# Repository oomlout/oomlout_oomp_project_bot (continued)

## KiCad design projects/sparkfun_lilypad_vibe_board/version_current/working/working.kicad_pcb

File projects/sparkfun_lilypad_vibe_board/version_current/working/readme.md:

# LilyPad_Vibe_Board by sparkfun  
This is a harvested standardized copy of a project from github.  
The original project can be found at:  
https://github.com/sparkfun/LilyPad_Vibe_Board  
Please consult that link for additional, details, files, and license information.  
Note: It was auto harvested and if the original repo had more than one board file or anything out of the ordinary the files here are likely not representative.

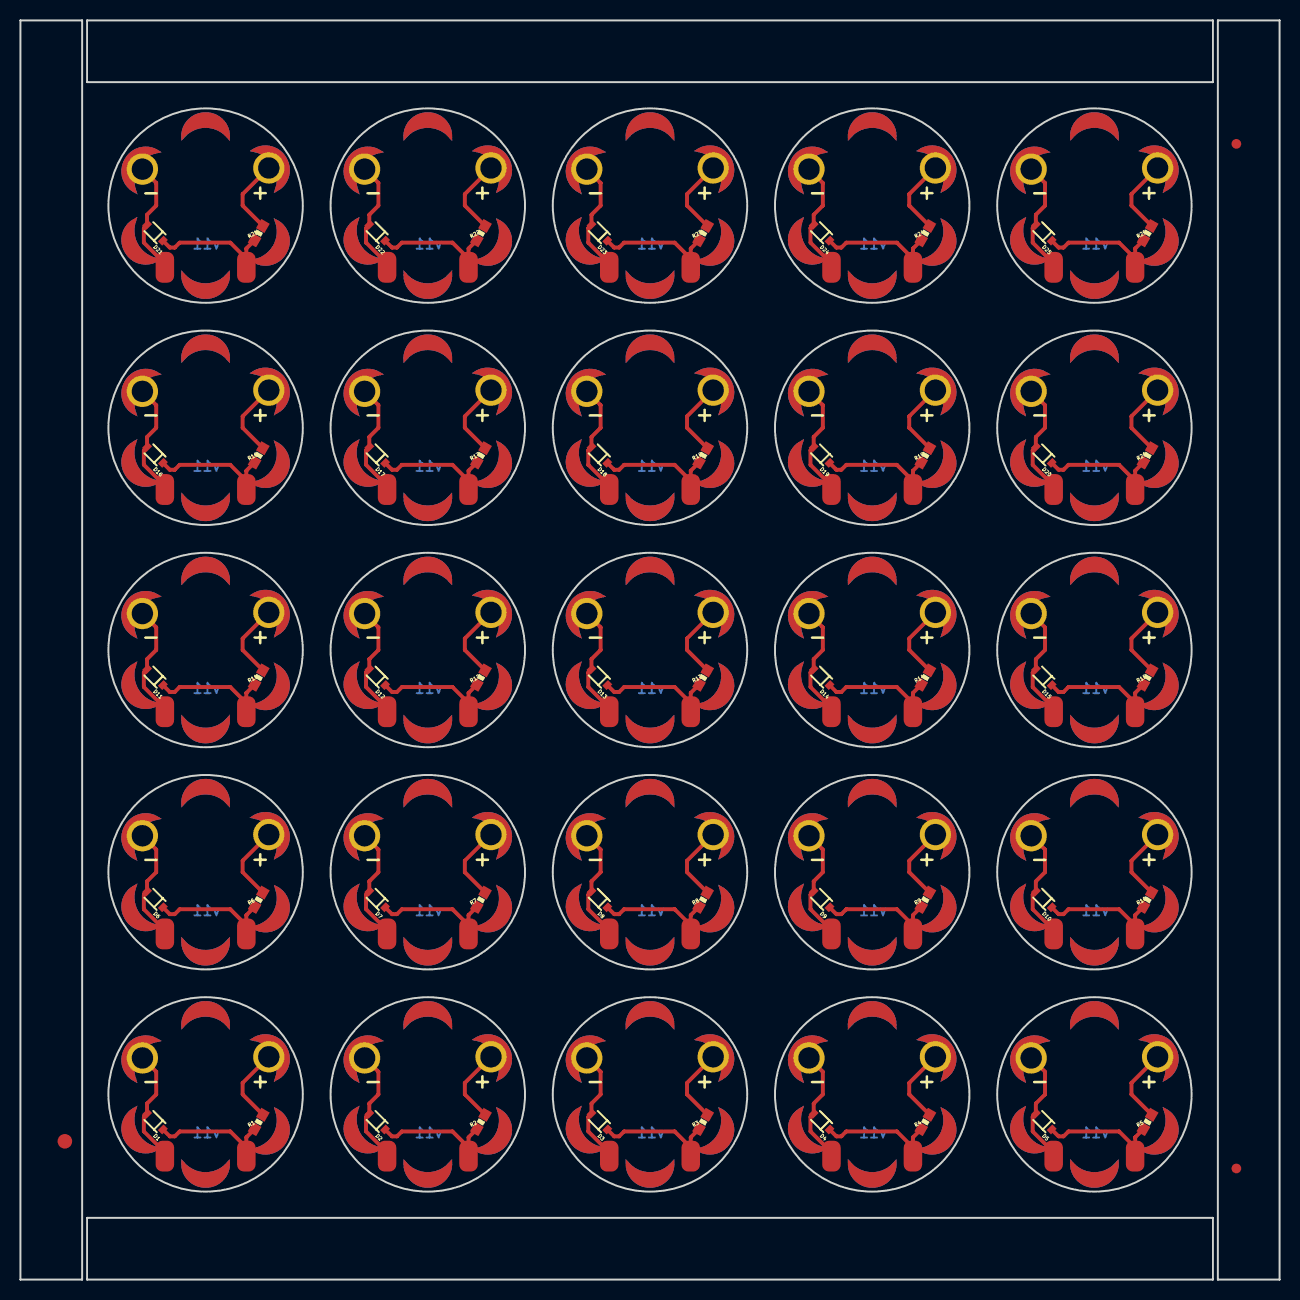
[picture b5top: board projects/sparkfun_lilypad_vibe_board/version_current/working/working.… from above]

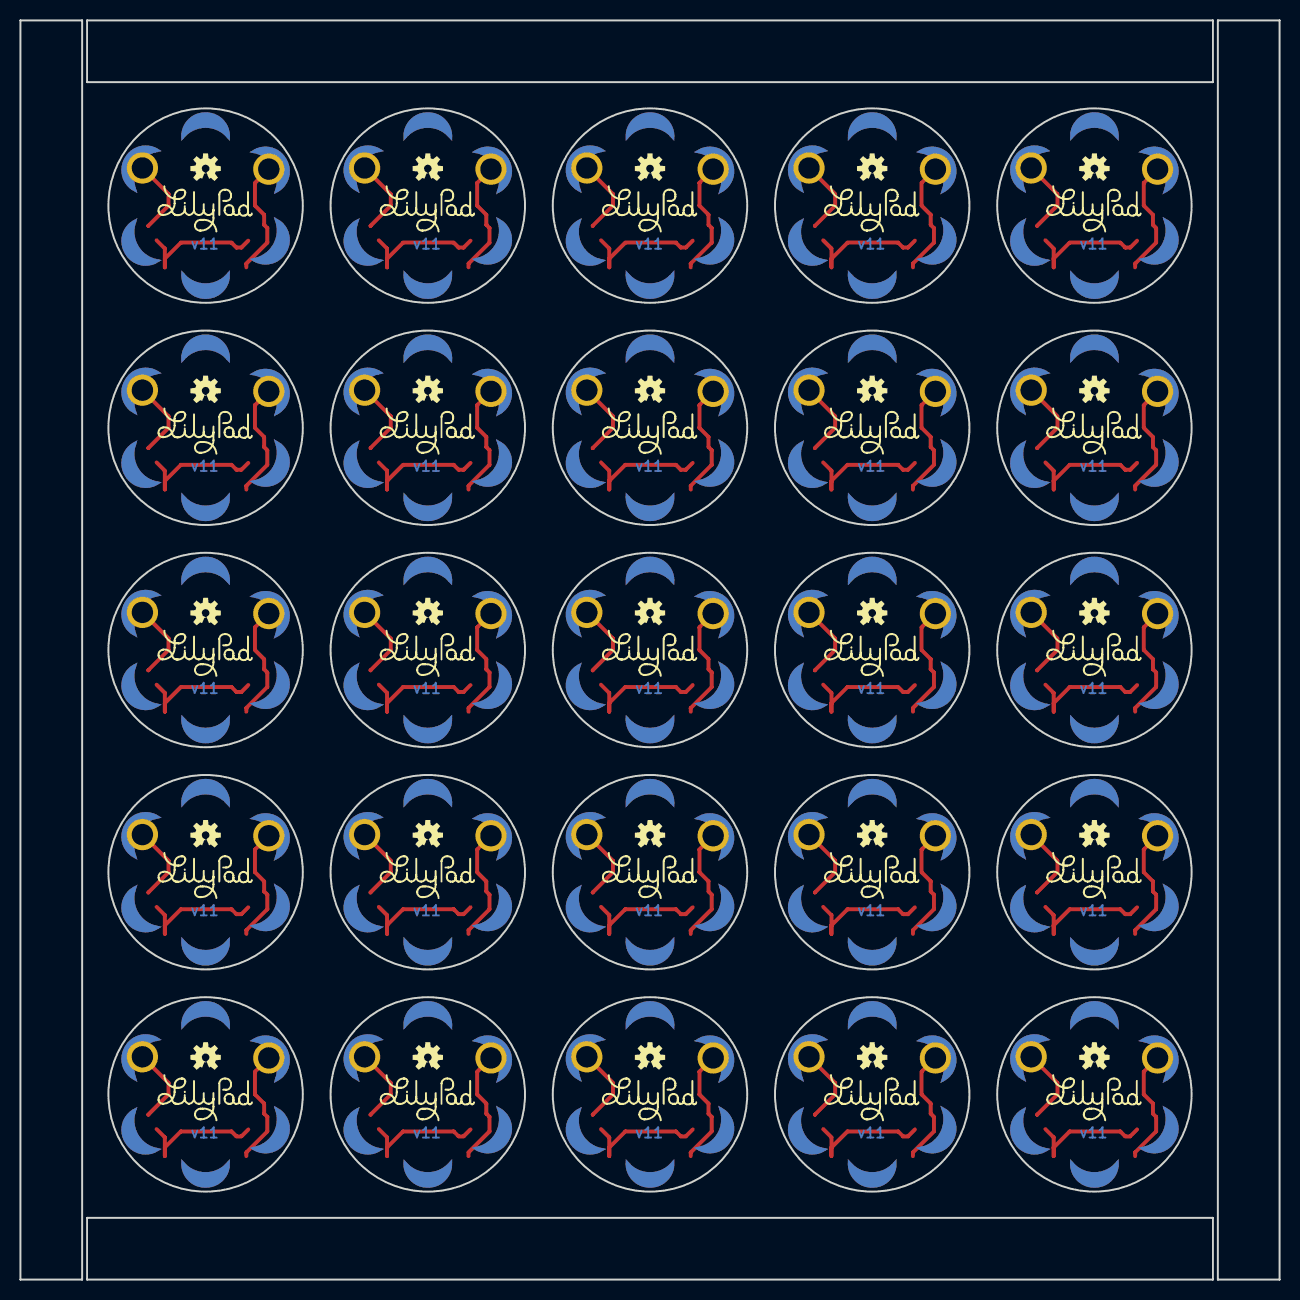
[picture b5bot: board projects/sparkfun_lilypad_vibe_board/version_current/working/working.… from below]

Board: 2 copper layers, 129.5 x 129.5 mm, 278 parts (50 on the bottom side), 75 nets.

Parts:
D1, D2, D3, D4, D5, D6, D7, D8, D9, D10, D11, D12, D13, D14, D15, D16, D17, D18, D19, D20, D21, D22, D23, D24, D25: SOD-323
E$1: FIDUCIAL-1.5X3
E$4, E$5: FIDUCIAL-1X2
LOGO1, LOGO2, LOGO3, LOGO4, LOGO5, LOGO6, LOGO7, LOGO8, LOGO9, LOGO10, LOGO11, LOGO12, LOGO13, LOGO14, LOGO15, LOGO16, LOGO17, LOGO18, LOGO19, LOGO20, LOGO21, LOGO22, LOGO23, LOGO24, LOGO25: OSHW-LOGOS; OSHW-LOGO-S
M1, M2, M3, M4, M5, M6, M7, M8, M9, M10, M11, M12, M13, M14, M15, M16, M17, M18, M19, M20, M21, M22, M23, M24, M25: MOTORSMD; VIBE-MOTOR-10MM-SMD
R1, R2, R3, R4, R5, R6, R7, R8, R9, R10, R11, R12, R13, R14, R15, R16, R17, R18, R19, R20, R21, R22, R23, R24, R25: 33; 0603-RES
U$1, U$2, U$3, U$4, U$5, U$6, U$7, U$8, U$9, U$10, U$11, U$12, U$13, U$14, U$15, U$16, U$17, U$18, U$19, U$20, U$21, U$22, U$23, U$24, U$25: LOGO-LPLP; LOGO-LILYPAD
VIBE1, VIBE3, VIBE4, VIBE5, VIBE7, VIBE8, VIBE9, VIBE11, VIBE12, VIBE13, VIBE15, VIBE16, VIBE17, VIBE19, VIBE20, VIBE21, VIBE23, VIBE24, VIBE25, VIBE27, VIBE28, VIBE29, VIBE31, VIBE32, VIBE33, VIBE35, VIBE36, VIBE37, VIBE39, VIBE40, VIBE41, VIBE43, VIBE44, VIBE45, VIBE47, VIBE48, VIBE49, VIBE51, VIBE52, VIBE53, VIBE55, VIBE56, VIBE57, VIBE59, VIBE60, VIBE61, VIBE63, VIBE64, VIBE65, VIBE67, VIBE68, VIBE69, VIBE71, VIBE72, VIBE73, VIBE75, VIBE76, VIBE77, VIBE79, VIBE80, VIBE81, VIBE83, VIBE84, VIBE85, VIBE87, VIBE88, VIBE89, VIBE91, VIBE92, VIBE93, VIBE95, VIBE96, VIBE97, VIBE99, VIBE100: SEWTAP-NOHOLE2; PETAL-NOHOLE-2SIDE
VIBE2, VIBE6, VIBE10, VIBE14, VIBE18, VIBE22, VIBE26, VIBE30, VIBE34, VIBE38, VIBE42, VIBE46, VIBE50, VIBE54, VIBE58, VIBE62, VIBE66, VIBE70, VIBE74, VIBE78, VIBE82, VIBE86, VIBE90, VIBE94, VIBE98: SEWTAP-NOHOLEW-MASK; PETAL-NOHOLE-2SIDE-SPECIAL-W-MASK
VIBE+0, VIBE+1, VIBE+2, VIBE+3, VIBE+4, VIBE+5, VIBE+6, VIBE+7, VIBE+8, VIBE+9, VIBE+10, VIBE+11, VIBE+12, VIBE+13, VIBE+14, VIBE+15, VIBE+16, VIBE+17, VIBE+18, VIBE+19, VIBE+20, VIBE+21, VIBE+22, VIBE+23, VIBE+24: SEWTAP6; PETAL-SMALL-2SIDE
VIBE-0, VIBE-1, VIBE-2, VIBE-3, VIBE-4, VIBE-5, VIBE-6, VIBE-7, VIBE-8, VIBE-9, VIBE-10, VIBE-11, VIBE-12, VIBE-13, VIBE-14, VIBE-15, VIBE-16, VIBE-17, VIBE-18, VIBE-19, VIBE-20, VIBE-21, VIBE-22, VIBE-23, VIBE-24: SEWTAP6; PETAL-SMALL-2SIDE

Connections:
5V: R1.2, VIBE+0.1
5V1: R2.2, VIBE+1.1
5V2: R3.2, VIBE+2.1
5V3: R4.2, VIBE+3.1
5V4: R5.2, VIBE+4.1
5V5: R6.2, VIBE+5.1
5V6: R7.2, VIBE+6.1
5V7: R8.2, VIBE+7.1
5V8: R9.2, VIBE+8.1
5V9: R10.2, VIBE+9.1
5V10: R11.2, VIBE+10.1
5V11: R12.2, VIBE+11.1
5V12: R13.2, VIBE+12.1
5V13: R14.2, VIBE+13.1
5V14: R15.2, VIBE+14.1
5V15: R16.2, VIBE+15.1
5V16: R17.2, VIBE+16.1
5V17: R18.2, VIBE+17.1
5V18: R19.2, VIBE+18.1
5V19: R20.2, VIBE+19.1
5V20: R21.2, VIBE+20.1
5V21: R22.2, VIBE+21.1
5V22: R23.2, VIBE+22.1
5V23: R24.2, VIBE+23.1
5V24: R25.2, VIBE+24.1
GND: D1.2, M1.P$2, VIBE-0.1
GND1: D2.2, M2.P$2, VIBE-1.1
GND2: D3.2, M3.P$2, VIBE-2.1
GND3: D4.2, M4.P$2, VIBE-3.1
GND4: D5.2, M5.P$2, VIBE-4.1
GND5: D6.2, M6.P$2, VIBE-5.1
GND6: D7.2, M7.P$2, VIBE-6.1
GND7: D8.2, M8.P$2, VIBE-7.1
GND8: D9.2, M9.P$2, VIBE-8.1
GND9: D10.2, M10.P$2, VIBE-9.1
GND10: D11.2, M11.P$2, VIBE-10.1
GND11: D12.2, M12.P$2, VIBE-11.1
GND12: D13.2, M13.P$2, VIBE-12.1
GND13: D14.2, M14.P$2, VIBE-13.1
GND14: D15.2, M15.P$2, VIBE-14.1
GND15: D16.2, M16.P$2, VIBE-15.1
GND16: D17.2, M17.P$2, VIBE-16.1
GND17: D18.2, M18.P$2, VIBE-17.1
GND18: D19.2, M19.P$2, VIBE-18.1
GND19: D20.2, M20.P$2, VIBE-19.1
GND20: D21.2, M21.P$2, VIBE-20.1
GND21: D22.2, M22.P$2, VIBE-21.1
GND22: D23.2, M23.P$2, VIBE-22.1
GND23: D24.2, M24.P$2, VIBE-23.1
GND24: D25.2, M25.P$2, VIBE-24.1
unnamed: D1.1, M1.P$1, R1.1
unnamed: D2.1, M2.P$1, R2.1
unnamed: D3.1, M3.P$1, R3.1
unnamed: D4.1, M4.P$1, R4.1
unnamed: D5.1, M5.P$1, R5.1
unnamed: D6.1, M6.P$1, R6.1
unnamed: D7.1, M7.P$1, R7.1
unnamed: D8.1, M8.P$1, R8.1
unnamed: D9.1, M9.P$1, R9.1
unnamed: D10.1, M10.P$1, R10.1
unnamed: D11.1, M11.P$1, R11.1
unnamed: D12.1, M12.P$1, R12.1
unnamed: D13.1, M13.P$1, R13.1
unnamed: D14.1, M14.P$1, R14.1
unnamed: D15.1, M15.P$1, R15.1
unnamed: D16.1, M16.P$1, R16.1
unnamed: D17.1, M17.P$1, R17.1
unnamed: D18.1, M18.P$1, R18.1
unnamed: D19.1, M19.P$1, R19.1
unnamed: D20.1, M20.P$1, R20.1
unnamed: D21.1, M21.P$1, R21.1
unnamed: D22.1, M22.P$1, R22.1
unnamed: D23.1, M23.P$1, R23.1
unnamed: D24.1, M24.P$1, R24.1
unnamed: D25.1, M25.P$1, R25.1

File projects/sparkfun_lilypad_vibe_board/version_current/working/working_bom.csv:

Row,Description,Part,References,Value,Footprint,Quantity Per PCB,Status,Datasheet
1,,DIODESOD,D1,DIODESOD,SOD-323,1, ,
2,,FRAME-LETTER,FRAME1,FRAME-LETTER,CREATIVE_COMMONS,1, ,
3,,OSHW-LOGOS,LOGO1,OSHW-LOGOS,OSHW-LOGO-S,1, ,
4,,MOTORSMD,M1,MOTORSMD,VIBE-MOTOR-10MM-SMD,1, ,
5,,33K-1%,R1,33,0603-RES,1, ,
6,,LOGO-LPLP,U$2,LOGO-LPLP,LOGO-LILYPAD,1, ,
7,,SEWTAP-NOHOLE2,VIBE1 VIBE3 VIBE4,SEWTAP-NOHOLE2,PETAL-NOHOLE-2SIDE,3, ,
8,,SEWTAP-NOHOLEW-MASK,VIBE2,SEWTAP-NOHOLEW-MASK,PETAL-NOHOLE-2SIDE-SPECIAL-W-MASK,1, ,
9,,SEWTAP6,VIBE+0 VIBE-0,SEWTAP6,PETAL-SMALL-2SIDE,2, ,





Project info:
Schematic:,working
Variant:,default
Revision:,
Date:,2023-08-06_12-56-04
KiCad Version:,7.0.6-7.0.6~ubuntu22.04.1
Statistics:
Component Groups:,9
Component Count:,12 (0 SMD/ 0 THT)
Fitted Components:,12 (0 SMD/ 0 THT)
Number of PCBs:,1
Total Components:,12

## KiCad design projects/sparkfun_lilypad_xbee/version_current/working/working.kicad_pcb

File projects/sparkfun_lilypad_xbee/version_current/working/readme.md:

# OOMP Project  
## LilyPad_XBee  by sparkfun  
  
oomp key: oomp_projects_flat_sparkfun_lilypad_xbee  
(snippet of original readme)  
  
LilyPad XBee  
============  
  
[  
*LilyPad XBee (DEV-08937)*](https://www.sparkfun.com/products/8937)  
  
The LilyPad Xbee is a breakout board for the popular XBee modules.   
Board includes easy-to-sew tabs and all the necessary power regulation to run on the LilyPad system.   
  
Repository Contents  
-------------------  
  
* **/Hardware** - All Eagle design files (.brd, .sch, .STL)  
* **/Production** - Test bed files and production panel files  

License Information  
-------------------  
The hardware is released under [Creative Commons ShareAlike 4.0 International](https://creativecommons.org/licenses/by-sa/4.0/).  
  
Distributed as-is; no warranty is given.  
  
  full source readme at [readme_src.md](readme_src.md)  
  
source repo at: [https://github.com/sparkfun/LilyPad_XBee](https://github.com/sparkfun/LilyPad_XBee)  
## Board  

## Schematic  

[schematic pdf](working_schematic.pdf)  
## Images

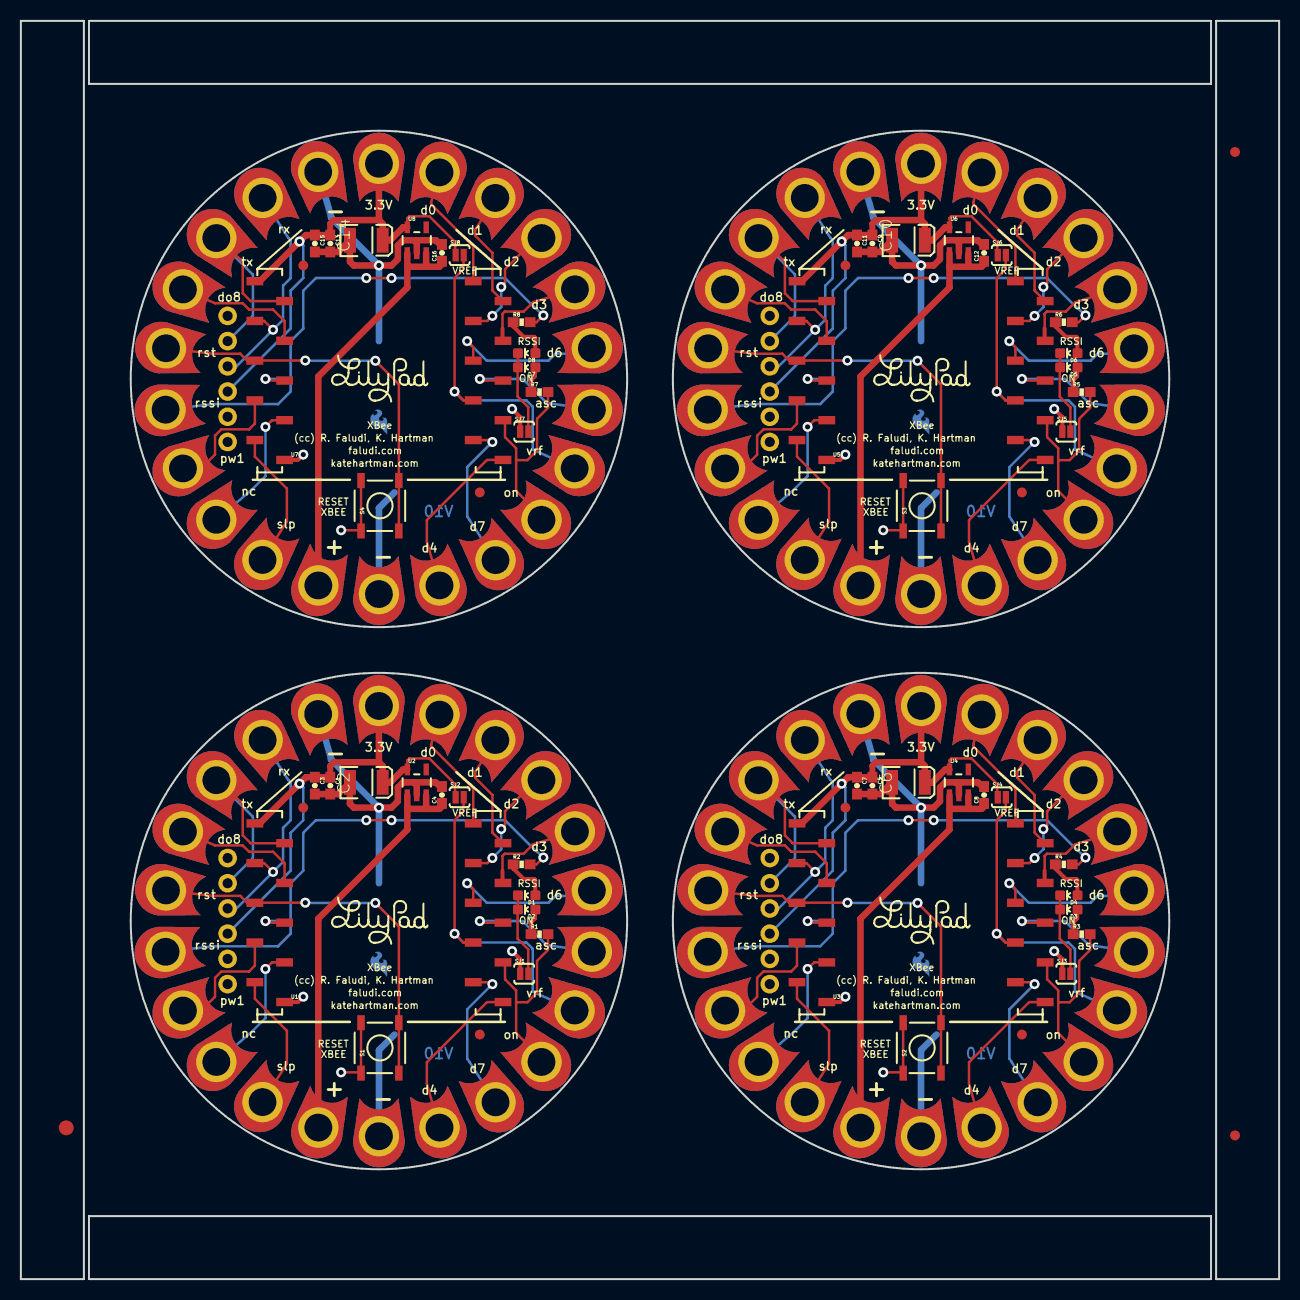
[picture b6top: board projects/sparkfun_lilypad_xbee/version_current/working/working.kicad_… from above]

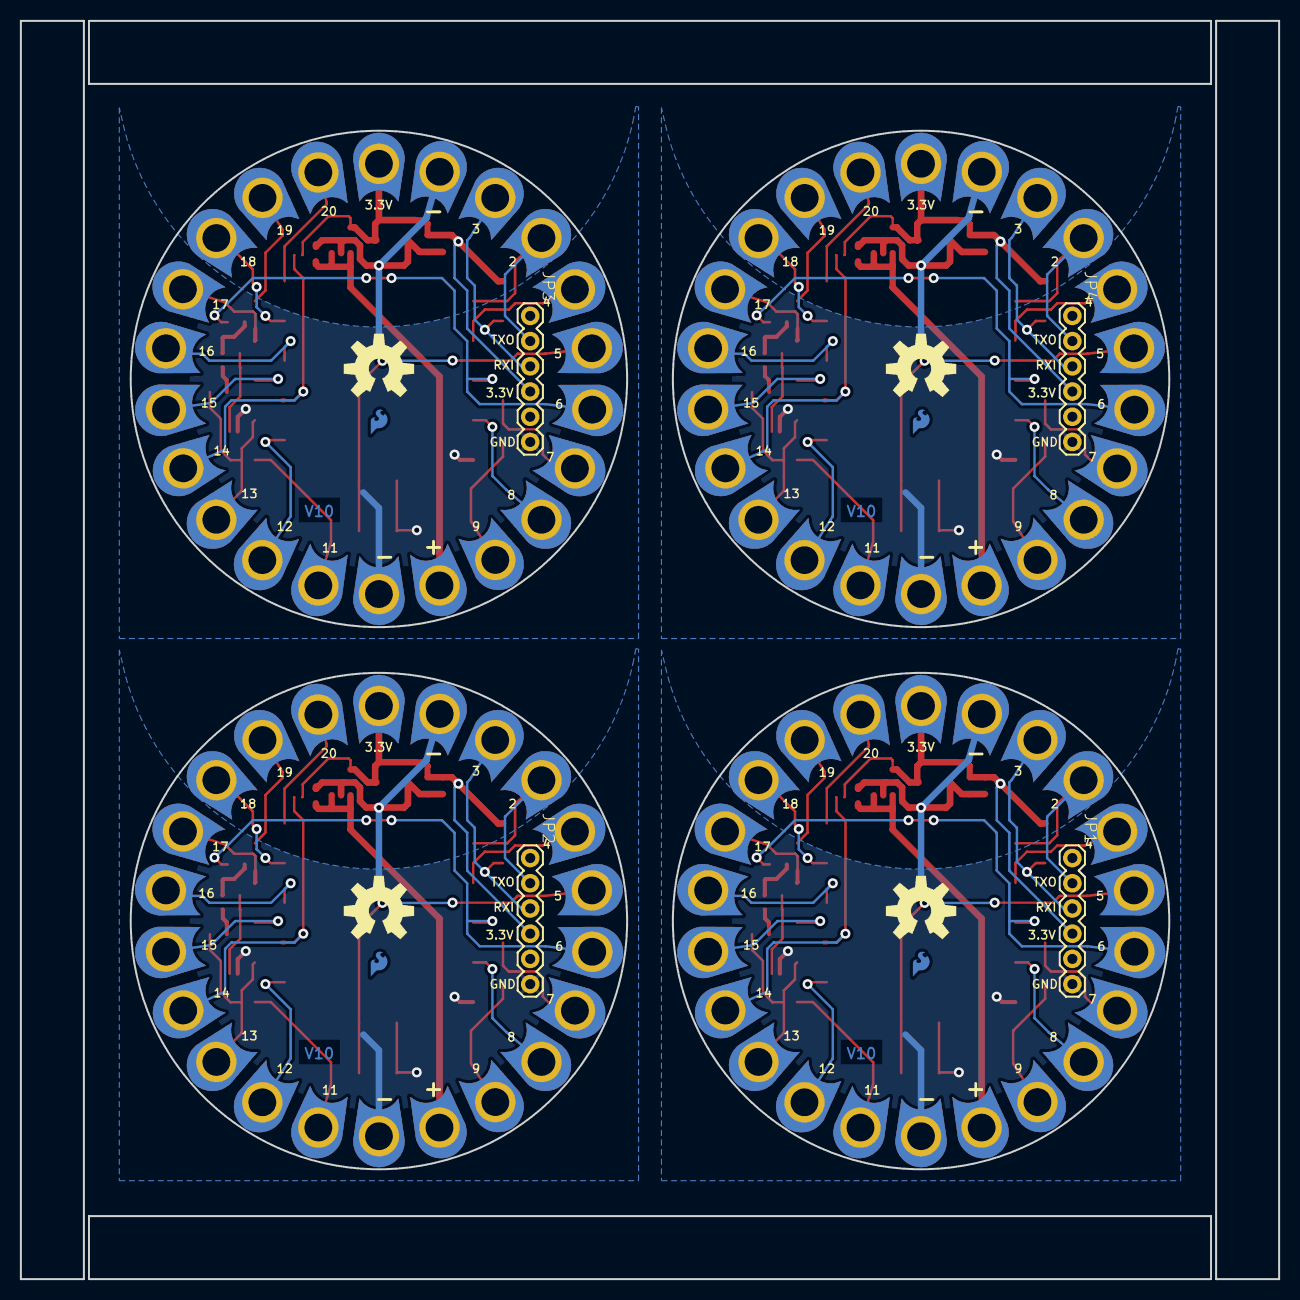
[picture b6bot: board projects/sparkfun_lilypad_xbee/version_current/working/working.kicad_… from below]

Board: 2 copper layers, 126.7 x 126.7 mm, 167 parts (12 on the bottom side), 96 nets.

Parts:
C1, C5, C9, C13: 0.1uF; 0603-CAP
C2, C6, C10, C14: 47uF; EIA3528
C3, C4, C7, C8, C11, C12, C15, C16: 1.0uF; 0603-CAP
D1, D2, D3, D4, D5, D6, D7, D8: Status; LED-0603
E$1: FIDUCIAL-1.5X3
E$4, E$6: FIDUCIAL-1X2
FID1, FID2, FID3, FID4, FID5, FID6, FID7, FID8: FIDUCIAL1X2; FIDUCIAL-1X2
GND0, GND1, GND2, GND3: SEWTAP9; PETAL-LONG-1-2SIDE
JP1, JP2, JP3, JP4: 1X06
LOGO1, LOGO2, LOGO3, LOGO4: SFE_LOGO_FLAME.1COP; SFE_LOGO_FLAME_COPPER_.1
R1, R2, R3, R4, R5, R6, R7, R8: 330; 0603-RES
S1, S2, S3, S4: TACTILE_SWITCH_SMD
SJ1, SJ2, SJ3, SJ4, SJ5, SJ6, SJ7, SJ8: SJ_2S-NOTRACE
U1, U3, U5, U7: XBEE-1B3; XBEE-SMD
U2, U4, U6, U8: V_REG_LDOSMD; SOT23-5
U$1, U$25, U$68, U$91: LOGO-LPLP; LOGO-LILYPAD
U$2, U$26, U$69, U$92: OSHW-LOGO-L
U$3, U$4, U$5, U$6, U$7, U$8, U$9, U$10, U$11, U$12, U$13, U$14, U$15, U$16, U$17, U$18, U$19, U$20, U$21, U$22, U$23, U$24, U$27, U$28, U$29, U$30, U$31, U$32, U$33, U$34, U$35, U$36, U$37, U$38, U$39, U$40, U$41, U$42, U$43, U$44, U$45, U$46, U$47, U$48, U$49, U$50, U$51, U$52, U$53, U$54, U$55, U$56, U$57, U$58, U$59, U$60, U$61, U$62, U$63, U$64, U$65, U$66, U$67, U$70, U$71, U$72, U$73, U$74, U$75, U$76, U$77, U$78, U$79, U$80, U$81, U$82, U$83, U$84, U$85, U$86, U$87, U$88, U$89, U$90: SEWTAP9; PETAL-LONG-1-2SIDE

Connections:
3.3V: C1.1, C2.A, C3.1, JP1.4, SJ2.1, U1.1, U2.5, U$47.1
3.3V1: C5.1, C6.A, C7.1, JP2.4, SJ4.1, U3.1, U4.5, U$21.1
3.3V2: C9.1, C10.A, C11.1, JP3.4, SJ6.1, U5.1, U6.5, U$64.1
3.3V3: C13.1, C14.A, C15.1, JP4.4, SJ8.1, U7.1, U8.5, U$87.1
CTS: U1.12, U$38.1
CTS1: U3.12, U$12.1
CTS2: U5.12, U$55.1
CTS3: U7.12, U$78.1
D0: U1.20, U$34.1
D1: U1.19, U$33.1
D2: U1.18, U$32.1
D3: U1.17, U$31.1
D4: U1.11, U$37.1
D5: U1.15, U$4.1
D6: U3.4, U$17.1
D7: U3.7, U$16.1
D8: U3.11, U$11.1
D9: U3.15, U$24.1
D10: U3.17, U$5.1
D11: U1.7, U$42.1
D12: U1.4, U$43.1
D13: U3.18, U$6.1
D14: U3.19, U$7.1
D15: U3.20, U$8.1
D16: U5.4, U$60.1
D17: U5.7, U$59.1
D18: U5.11, U$54.1
D19: U5.15, U$67.1
D20: U5.17, U$28.1
D21: U5.18, U$29.1
D22: U5.19, U$49.1
D23: U5.20, U$50.1
D24: U7.4, U$83.1
D25: U7.7, U$82.1
D26: U7.11, U$77.1
D27: U7.15, U$90.1
D28: U7.17, U$71.1
D29: U7.18, U$72.1
D30: U7.19, U$73.1
D31: U7.20, U$74.1
DTR: U1.9, U$48.1
DTR1: U3.9, U$22.1
DTR2: U5.9, U$65.1
DTR3: U7.9, U$88.1
GND: C1.2, C2.C, C3.2, C4.2, JP1.6, S1.1, S1.2, SJ1.1, U1.10, U2.2, U$36.1, U$46.1
GND1: C5.2, C6.C, C7.2, C8.2, JP2.6, S2.1, S2.2, SJ3.1, U3.10, U4.2, U$10.1, U$20.1
GND2: C9.2, C10.C, C11.2, C12.2, JP3.6, S3.1, S3.2, SJ5.1, U5.10, U6.2, U$53.1, U$63.1
GND3: C13.2, C14.C, C15.2, C16.2, JP4.6, S4.1, S4.2, SJ7.1, U7.10, U8.2, U$76.1, U$86.1
unnamed: D1.A, R2.1
unnamed: D2.A, R1.1
unnamed: D1.C, D2.C, SJ1.2
unnamed: D3.A, R3.1
unnamed: D4.A, R4.1
unnamed: D3.C, D4.C, SJ3.2
unnamed: D5.A, R5.1
unnamed: D6.A, R6.1
unnamed: D5.C, D6.C, SJ5.2
unnamed: D7.A, R7.1
unnamed: D8.A, R8.1
unnamed: D7.C, D8.C, SJ7.2
ON: R1.2, U1.13, U$39.1
ON1: R3.2, U3.13, U$13.1
ON2: R5.2, U5.13, U$56.1
ON3: R7.2, U7.13, U$79.1
RES: U1.8, U$41.1
RES1: U3.8, U$15.1
RES2: U5.8, U$58.1
RES3: U7.8, U$81.1
RESET: GND0.1, S1.3, S1.4, U1.5
RESET1: GND1.1, S2.3, S2.4, U3.5
RESET2: GND2.1, S3.3, S3.4, U5.5
RESET3: GND3.1, S4.3, S4.4, U7.5
RSSI: R2.2, U1.6, U$51.1
RSSI1: R4.2, U3.6, U$23.1
RSSI2: R6.2, U5.6, U$66.1
RSSI3: R8.2, U7.6, U$89.1
RTS: U1.16, U$30.1
RTS1: U3.16, U$3.1
RTS2: U5.16, U$27.1
RTS3: U7.16, U$70.1
RX-I: JP1.3, U1.3, U$45.1
RX-I1: JP2.3, U3.3, U$19.1
RX-I2: JP3.3, U5.3, U$62.1
RX-I3: JP4.3, U7.3, U$85.1
TX-O: JP1.2, U1.2, U$44.1
TX-O1: JP2.2, U3.2, U$18.1
TX-O2: JP3.2, U5.2, U$61.1
TX-O3: JP4.2, U7.2, U$84.1
VCC: C4.1, U2.1, U2.3, U$35.1
VCC1: C8.1, U4.1, U4.3, U$9.1
VCC2: C12.1, U6.1, U6.3, U$52.1
VCC3: C16.1, U8.1, U8.3, U$75.1
VREF: SJ2.2, U1.14, U$40.1
VREF1: SJ4.2, U3.14, U$14.1
VREF2: SJ6.2, U5.14, U$57.1
VREF3: SJ8.2, U7.14, U$80.1
